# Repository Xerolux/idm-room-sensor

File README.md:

<div align="center">

# IDM Smart Climate Platform

**Open-source climate bridge, room sensing and condensation protection for IDM heat pumps**

</div>

> [!CAUTION]
> **Experimental developer edition. Not production-ready and not validated on a real IDM installation.**  
> Do not connect unverified hardware to a heat pump. Independent condensation protection remains mandatory for cooling tests.

<!-- SAFETY:NOT_PRODUCTION --><!-- SAFETY:WORK_IN_PROGRESS -->

## What this project contains

The platform combines three hardware approaches and a software-first GLT bridge:

| Component | Purpose | Status |
|---|---|---|
| ESP Room Sensor | Local SHT45 sensing, ESPHome, 0–10 V humidity and real KTY81-210 | Design prototype |
| Classic Sensor | Compact local sensor without Wi-Fi | Design prototype |
| Fake Sensor / Bridge | Receives HA/KNX/MQTT values and emulates the original IDM interface | Design prototype |
| Climate Engine | Selects the most critical room by dew-point margin | Functional HA example |
| `set_external_climate` | Native service present on `idm-heatpump-hass` main; stable-package fallback included here | Software tested, real device untested |
| Pipe Dew-Point Guard | Independent pipe-temperature/condensation safety concept | Documentation only |

## Confirmed original sensor information

The available LCN-FTW04 documentation identifies a combined room humidity/temperature sensor, a 0–10 V humidity output, KTY temperature element and 14–30 V DC supply. Only one room humidity sensor is intended for the Navigator; individual room temperatures may come from room units.

Current project terminal mapping must be verified against the exact IDM wiring diagram before connection:

| Function | Project signal |
|---|---|
| Supply | 14–30 V DC |
| Humidity | 0–10 V, working assumption 0–100 % RH |
| Temperature | KTY81-210 equivalent |
| Ground | Common reference |

## Preferred architecture

```text
KNX / ESPHome / Zigbee / MQTT room sensors
                    │
                    ▼
        Home Assistant Climate Engine
        - dew point per room
        - minimum dew-point margin
        - stale sensor detection
        - configurable fallback
                    │
          ┌─────────┴─────────┐
          ▼                   ▼
 GLT / Modbus registers   Analog fallback bridge
 1650…1663 temperature    0–10 V humidity
 1692 humidity            KTY emulation
          │                   │
          └─────────┬─────────┘
                    ▼
               IDM Navigator

Independent pipe dew-point switch / cooling inhibit
```

## Project checklist

### Documentation and repository
- [x] Professional README
- [x] GitHub Pages / Docsify structure
- [x] Wiki source pages
- [x] Issue and pull-request templates
- [x] Security, contributing and code-of-conduct files
- [x] Community test forms
- [x] Architecture and safety documentation

### Home Assistant and IDM integration
- [x] Multi-room climate-engine package selecting the highest dew point
- [x] Example automation for GLT register writes
- [x] Stale-input detection using Home Assistant `last_reported`
- [x] `set_external_climate` reference aligned with current upstream interfaces
- [x] Local service-contract and dew-point tests
- [x] Current register mapping reviewed against `idm-heatpump-api` main
- [ ] Release `set_external_climate` in a tagged `idm-heatpump-hass` version
- [ ] Real-device Modbus verification
- [ ] Confirm that the selected IDM configuration uses GLT values for cooling control

### ESPHome and firmware
- [x] ESPHome bridge configuration
- [x] Home Assistant-controlled temperature/humidity inputs
- [x] Stale-data timeout and conservative fallback concept
- [x] Dew-point calculation example
- [x] MCP4725 output component source
- [x] KTY lookup and calibration framework
- [x] Compile against the selected ESPHome release
- [x] Local authenticated web UI with confirmation-gated calibration/reset
- [x] Native ESP-IDF target with I/O, fail-safe runtime, NVS, API and OTA
- [ ] Hardware-in-the-loop test
- [ ] OTA recovery test

### Hardware
- [x] Block-level schematics and KiCad project structure
- [x] Board outlines and component placement concepts
- [x] Preliminary BOM and JLCPCB templates
- [x] Enclosure STL/OpenSCAD prototypes
- [ ] Replace every prototype symbol/footprint with verified manufacturer footprint
- [ ] Complete ERC/DRC with KiCad 9
- [ ] Review switch-mode power-supply layout against regulator datasheet
- [ ] Route and validate analog ground/current return paths
- [ ] Manufacture prototype
- [ ] Validate 0–10 V linearity and load drive
- [ ] Validate KTY emulation excitation voltage/current
- [ ] EMC, ESD, thermal and long-term tests

### Real installation
- [ ] Measure the original sensor at multiple humidity points
- [ ] Measure IDM KTY input using a resistance decade
- [ ] Confirm safe open-circuit and short-circuit behavior
- [ ] Heating-only observation
- [ ] Cooling test with independent dew-point switch
- [ ] Multi-week logging and fault injection

## Quick start for contributors

1. Read [Safety](pages/#/cooling-safety) and [Validation Plan](pages/#/validation).
2. Choose the next unblocked item from the [prioritized task list](TASKS.md).
3. Do not mark measurements as verified without raw data and test conditions.
4. Open an issue using the measurement or hardware-test template.

## Repository layout

```text
hardware/                 KiCad prototypes, BOM, CPL templates, enclosures
firmware/                 ESPHome and custom component sources
homeassistant/            Climate engine, automations and dashboard examples
idm-heatpump-hass/        Upstream service patch and tests
pages/                    GitHub Pages / Docsify site
wiki/                     GitHub Wiki source pages
docs/                     Technical documentation and validation plans
manufacturing/            Shared fabrication notes and release checklist
.github/                  Workflows, issue templates and contribution automation
```

ESPHome and native ESP-IDF builds use the pinned toolchains documented in
[firmware/BUILDING.md](firmware/BUILDING.md).

## Safety

This project is unaffiliated with IDM Energiesysteme. It is experimental open hardware. Incorrect humidity or temperature values can defeat condensation protection and cause water damage. Use an independent, hard-wired pipe dew-point switch during development and commissioning.

## Community Work Packages

- `work-packages/WP01-hardware`
- `work-packages/WP02-firmware`
- `work-packages/WP03-home-assistant`
- `work-packages/WP04-documentation`
- `work-packages/WP05-validation`

See the [prioritized task list](TASKS.md) and the compact
[project-status summary](PROJECT_STATUS.md).

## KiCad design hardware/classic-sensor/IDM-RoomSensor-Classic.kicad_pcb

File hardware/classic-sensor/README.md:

# IDM-RoomSensor-Classic Rev. A

Enthalten: KiCad-Schaltplan, PCB-Layout/Platzierung, BOM, Firmware-Grundlage und Gehäuse als STL/OpenSCAD.

**Versorgung:** Die Classic-Platine wird aus den 24 V der IDM versorgt und besitzt kein WLAN/ESP.

IDM-Klemmen: 43=KTY-Temperatursignal, 42=+14–32 V DC, 41=gemeinsamer GND/KTY-Rückleiter, 40=Feuchte 0–10 V.

Annahme: 0 V = 0 % rF, 10 V = 100 % rF.

## Status
Rev.-A-Entwicklungsgrundlage, **nicht produktionsfreigegeben**. Vor Bestellung und Anschluss: Footprints, ERC/DRC, Analogskalierung, Schutzbeschaltung, EMV und reale IDM-Kennlinie prüfen und kalibrieren.

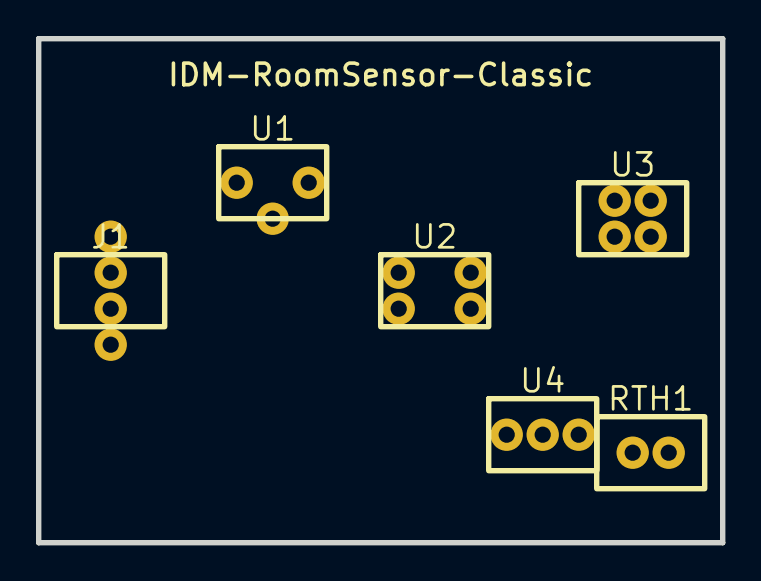
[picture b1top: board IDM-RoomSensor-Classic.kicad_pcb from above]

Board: 2 copper layers, 38.0 x 28.0 mm, 6 parts (0 on the bottom side), 7 nets, no tracks yet.

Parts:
J1: IDM_4PIN
RTH1: KTY81-210
U1: BUCK_24V_5V
U2: ATTINY1616
U3: SHT45
U4: MCP4725_OPA197

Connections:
+5V: U1.2, U2.1, U3.1, U4.1
+24V: J1.2, U1.1
GND: J1.3, RTH1.2, U1.3, U2.2, U3.2, U4.2
I2C_SCL: U2.4, U3.4
I2C_SDA: U2.3, U3.3
RH_0_10V: J1.4, U4.3
TEMP_KTY: J1.1, RTH1.1

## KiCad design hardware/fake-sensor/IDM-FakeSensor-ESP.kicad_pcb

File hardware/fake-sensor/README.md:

# IDM Fake Sensor ESP – Revision A

Diese Platine empfängt Temperatur- und Feuchtewerte aus Home Assistant und simuliert gegenüber der IDM AERO ALM den originalen Temperatur-/Feuchtesensor.

## Ausgänge

| IDM-Klemme | Signal |
|---|---|
| 43 | emuliertes KTY-Temperatursignal |
| 42 | +14–32 V DC Versorgung |
| 41 | gemeinsamer GND/KTY-Rückleiter |
| 40 | simulierte Feuchte 0–10 V |

Der ESP32 wird vollständig aus den 24 V der IDM versorgt.

## Home Assistant

Home Assistant setzt zwei ESPHome-Number-Entitäten:

- simulierte relative Feuchte
- simulierte Raumtemperatur

Damit können Mittelwerte, Maximalwerte oder der ungünstigste Raum an die Wärmepumpe weitergegeben werden. Für die Kühlung sollte eher der **kritischste Raum** verwendet werden als ein Durchschnitt.

## Fail-safe

Bei fehlenden Aktualisierungen werden standardmäßig ausgegeben:

- 80 % rF
- 28 °C

Die Werte sind absichtlich konservativ. Zusätzlich sollte die vorhandene Taupunktüberwachung der Anlage aktiv bleiben.

## Wichtige technische Einschränkung

Die Feuchtesimulation ist klar: DAC plus Operationsverstärker erzeugen 0–10 V.

Die Temperatursimulation muss noch elektrisch validiert werden. Der Entwurf verwendet einen Digitalpotentiometer plus Festwiderstandsnetzwerk zur Nachbildung eines KTY81-210. Vor Anschluss müssen an der IDM gemessen werden:

1. Leerlaufspannung an 43 gegen 41,
2. Messstrom durch einen echten KTY81-210,
3. zulässige Spannung an den Anschlüssen des Digitalpotentiometers,
4. tatsächliche Widerstandskennlinie, die die IDM erwartet.

Falls Spannung oder Strom für einen Digitalpotentiometer ungeeignet sind, muss die Temperaturstufe durch eine galvanisch isolierte Widerstandsmatrix oder PhotoMOS-Lösung ersetzt werden.

## Status des Layouts

Das KiCad-PCB enthält Boardkontur und Bauteilplatzierung. Es ist eine Rev.-A-Entwicklungsgrundlage und **nicht produktionsfreigegeben**. Vor Bestellung:

- Footprints kontrollieren,
- Schaltplan in modernes KiCad-Format übernehmen,
- vollständig routen,
- ERC/DRC ausführen,
- 0–10-V-Verstärkung dimensionieren,
- Temperaturstufe vermessen und kalibrieren,
- EMV- und Schutzbeschaltung prüfen.

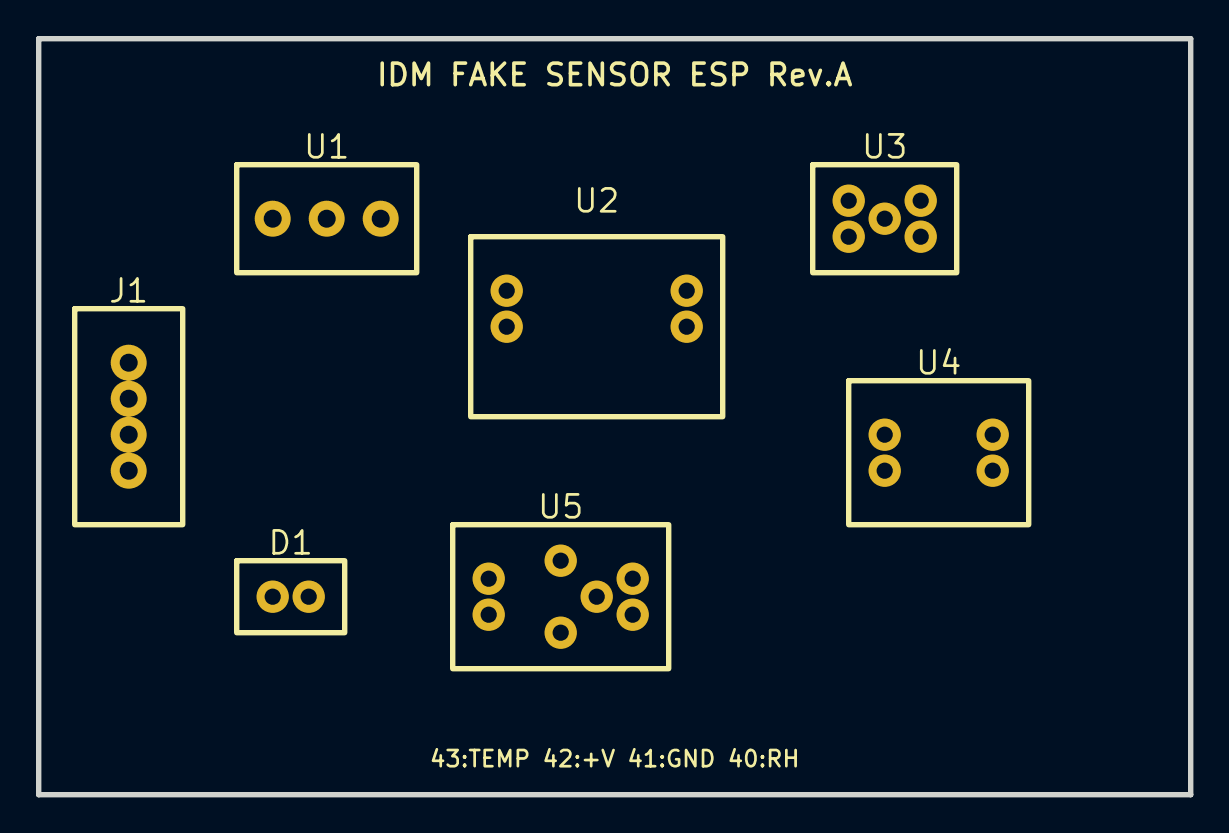
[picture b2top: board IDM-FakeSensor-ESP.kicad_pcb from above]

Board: 2 copper layers, 64.0 x 42.0 mm, 7 parts (0 on the bottom side), 8 nets, no tracks yet.

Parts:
D1: SMBJ30A; TVS_INPUT
J1: IDM; TERM_4P
U1: 24V_TO_5V; BUCK
U2: ESP32-C3-MINI-1; ESP32_C3_MINI
U3: MCP4725
U4: OPA197_GAIN; OPA197_0_10V
U5: AD5242BRUZ10; AD5242_DIGIPOT

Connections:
+3V3: U2.1, U3.1, U5.1
+24V: D1.1, J1.2, U1.1, U4.3
DAC_RAW: U3.5, U4.1
GND: D1.2, J1.3, U1.2, U2.2, U3.2, U4.2, U5.2
I2C_SCL: U2.4, U3.4, U5.4
I2C_SDA: U2.3, U3.3, U5.3
RH_0_10V: J1.4, U4.4
TEMP_A: J1.1, U5.5
